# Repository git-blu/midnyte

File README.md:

# Midnyte LED tablet

Midnyte is an AVR-based resistive touchscreen tablet that uses a 16x24 RGB LED display.
74HC595 shift registers and TLC5940 16-channel PWM LED drivers drive the display and a Semtech SX8652 drives the 4-wire resistive touch panel for user input.
The device can switch between wall power and an internal Li-Ion battery pack.

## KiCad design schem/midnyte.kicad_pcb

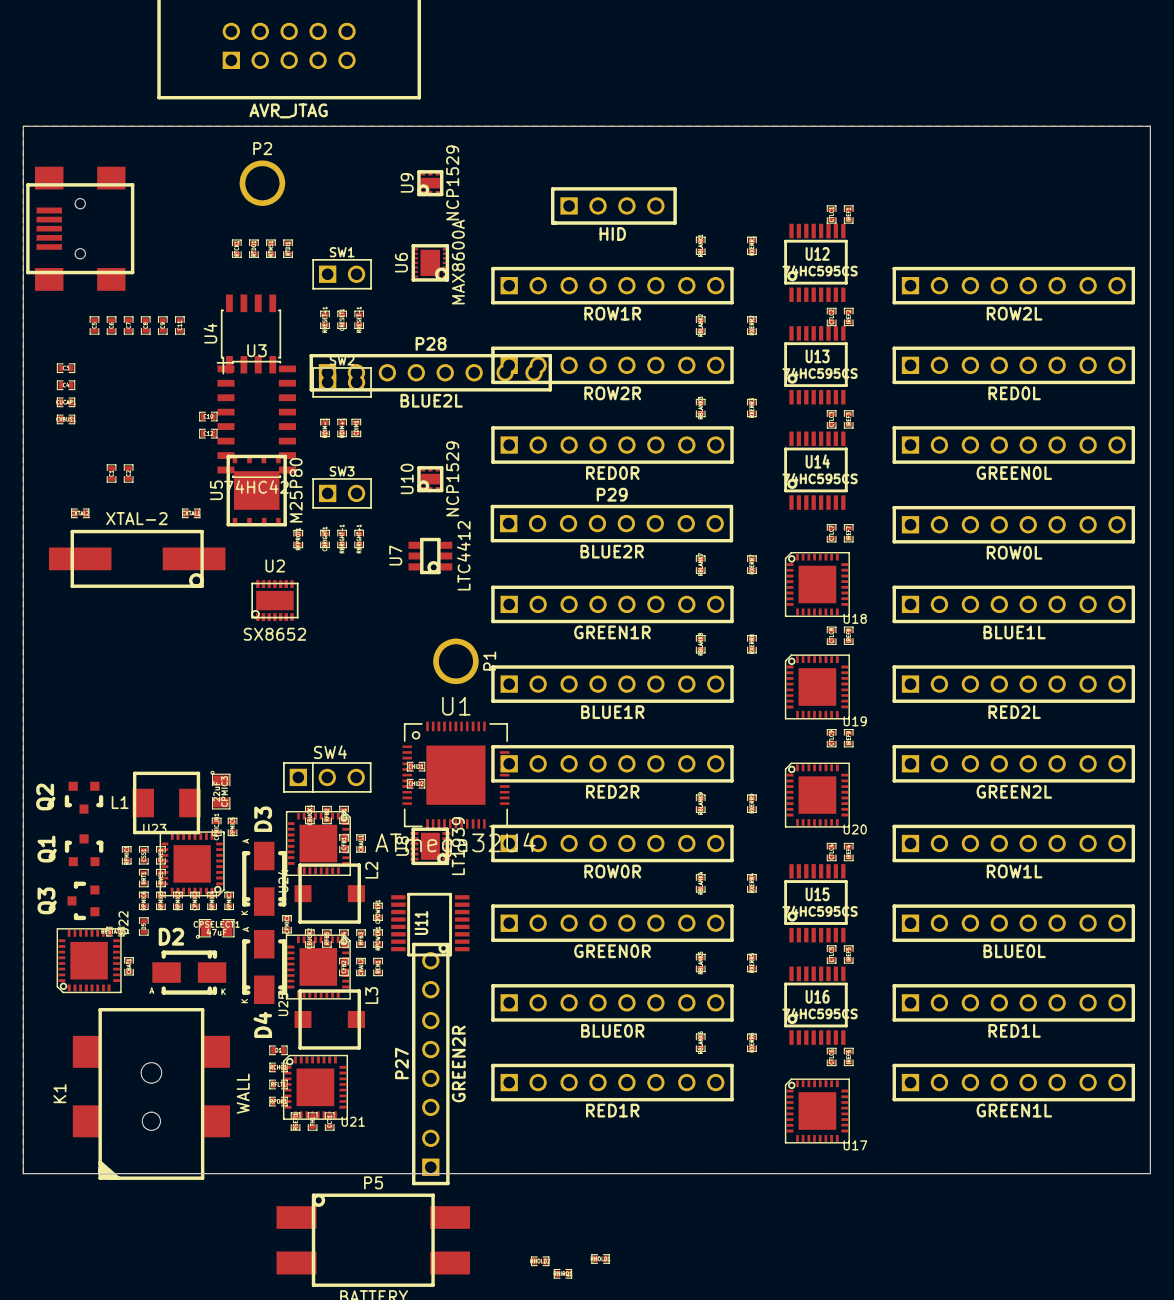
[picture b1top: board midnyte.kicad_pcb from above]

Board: 4 copper layers, 99.0 x 92.0 mm, 181 parts (0 on the bottom side), 302 nets, no tracks yet.

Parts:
C1, C2, C3, C4, C5, C6, C7, C8, C9, C10, C11, C12: 0.1uF; SMD-0402
CBAT1: 2.2uF; SMD-0402
CBRIGHT1: 0.1uF; SMD-0402
CBUCK1, CBUCK2: 4.7uF; SMD-0402
CCT1: 680nF; SMD-0402
CDIM1: 0.1uF; SMD-0402
CFB1, CFB2: 18pF; SMD-0402
CHID1: 1uF; SMD-0402
CHID2: 0.1uF; SMD-0402
CON1: USB-MINI-B; 10033526-N3212LF
CPMIC1: 0.47uF; SMD-0402
CPMIC2: 1uF; SMD-0402
CPMIC3: 22uF; SMD-0805
CPMIC_IN1: 2.2uF; SMD-0402
CPOWER1: 0.1uF; SMD-0402
CPSELECT1: 47uF; SMD-0805
CRAIL1, CRAIL2: 10uF; SMD-0402
CRESET1: 0.1uF; SMD-0402
CSS1: 0.47uF; SMD-0402
CTLC1, CTLC2, CTLC3, CTLC4, CTLC5, CTLC6, CTLC7, CTLC8, CTLC9: 0.1uF; SMD-0402
CUCAP1: 1uF; SMD-0402
CVBUS1: 0.1uF; SMD-0402
CVC1: 220pF; SMD-0402
CXTAL1, CXTAL2: 18pF; SMD-0402
D1, D5: DIODE; SMD-0402
D2, D3, D4: SCHOTTKY; Diode-SMA_Standard
IREF1, IREF2, IREF3, IREF4, IREF5, IREF6, IREF7, IREF8, IREF9: 7.68k; SMD-0402
K1: WALL; PJ-002AH-SMT
L1: 4.7uH; ASPI-0530LR-4R7M-T2
L2, L3: 2.2uH; LTF5022T-2R2N3R2-LC
P1, P2: HOLE-M3
P3: HID; pin_array_4x1
P4: AVR_JTAG; 302-S101
P5: BATTERY; 1954097-1
P6: ROW0L; pin_array_8x1
P7: ROW0R; pin_array_8x1
P8: ROW1L; pin_array_8x1
P9: ROW1R; pin_array_8x1
P10: ROW2L; pin_array_8x1
P11: ROW2R; pin_array_8x1
P12: RED0L; pin_array_8x1
P13: RED0R; pin_array_8x1
P14: GREEN0L; pin_array_8x1
P15: GREEN0R; pin_array_8x1
P16: BLUE0L; pin_array_8x1
P17: BLUE0R; pin_array_8x1
P18: RED1L; pin_array_8x1
P19: RED1R; pin_array_8x1
P20: GREEN1L; pin_array_8x1
P21: GREEN1R; pin_array_8x1
P22: BLUE1L; pin_array_8x1
P23: BLUE1R; pin_array_8x1
P24: RED2L; pin_array_8x1
P25: RED2R; pin_array_8x1
P26: GREEN2L; pin_array_8x1
P27: GREEN2R; pin_array_8x1
P28: BLUE2L; pin_array_8x1
P29: BLUE2R; pin_array_8x1
Q1, Q2: FQP27P06; SOT23_Transistor_RevB_14Mar2014
Q3: N-CHANNEL_FET; SOT23_Transistor_RevB_14Mar2014
RBLANK1, RBLANK2, RBLANK3, RBLANK4, RBLANK5, RBLANK6, RBLANK7, RBLANK8, RBLANK9: 10k; SMD-0402
RBRIGHT+1: 10k; SMD-0402
RBRIGHT-1: 100; SMD-0402
RCHG1: 660; SMD-0402
RDIM+1: 10k; SMD-0402
RDIM-1: 100; SMD-0402
REN1: 10k; SMD-0402
RFB1: 2.7M; SMD-0402
RFB2, RFB5: 597k; SMD-0402
RFB3: 4.32M; SMD-0402
RFB4: 80k; SMD-0402
RFLT1: 100k; SMD-0402
RFPROT1: 10k; SMD-0402
RHOLD1, RHOLD2: 10k; SMD-0402
RNIRQ1: 10k; SMD-0402
RPMIC1: 10k; SMD-0402
RPMIC2, RPMIC5: 42.2k; SMD-0402
RPMIC3, RPMIC6, RPMIC7: 8.06k; SMD-0402
RPMIC4: 100k; SMD-0402
RPOK1: 10k; SMD-0402
RPOWER1: 10k; SMD-0402
RPSTATUS1: 10k; SMD-0402
RRESET+1: 10k; SMD-0402
RRESET-1: 100; SMD-0402
RRT1: 40.2k; SMD-0402
RSETI1: 2k; SMD-0402
RTCK1: 100k; SMD-0402
RTDI1: 100k; SMD-0402
RTDO1: 100k; SMD-0402
RTMS1: 100k; SMD-0402
RVC1: 49.9k; SMD-0402
RXERR1, RXERR2, RXERR3, RXERR4, RXERR5, RXERR6, RXERR7, RXERR8, RXERR9: 10k; SMD-0402
SW1: RESET; pin_array_1x02
SW2: -BRIGHTNESS; pin_array_1x02
SW3: +BRIGHTNESS; pin_array_1x02
SW4: POWER; pin_array_1x03
TH1: 10k@25C; SMD-0402
U1: ATmega32U4; QFN-44-1EP
U2: SX8652
U3: 74HC42; SOIC-16_3.9x9.9mm_Pitch1.27mm
U4: 23LC1024; SOIC-8_3.9x4.9mm_Pitch1.27mm
U5: M25P80; VDFN-8
U6: MAX8600A; TDFN14
U7: LTC4412; TSOT-23
U8: LT1939; DFN12
U9, U10: NCP1529; UDFN6
U11, U12, U13, U14, U15, U16: 74HC595CS; TSSOP-16
U17, U18, U19, U20, U21, U22, U23, U24, U25: TLC5940; QFN-32-1EP
X1: XTAL-2; CSM-7X

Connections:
+3.3V: C1.1, C2.1, C3.1, C4.1, C5.1, C6.1, C7.1, C8.1, C9.1, C10.1, C11.1, C12.1, CFB1.1, CHID1.1, CHID2.1, CRAIL1.1, CTLC1.1, CTLC2.1, CTLC3.1, CTLC4.1, CTLC5.1, CTLC6.1, CTLC7.1, CTLC8.1, CTLC9.1, D1.1, L2.2, P4.4, RBLANK1.1, RBLANK2.1, RBLANK3.1, RBLANK4.1, RBLANK5.1, RBLANK6.1, RBLANK7.1, RBLANK8.1, RBLANK9.1, RBRIGHT+1.1, RDIM+1.1, RFB1.1, RFLT1.1, RFPROT1.1, RHOLD1.1, RHOLD2.1, RNIRQ1.1, RPMIC1.1, RPOK1.1, RPSTATUS1.1, RRESET+1.1, RTCK1.1, RTDI1.1, RTDO1.1, RTMS1.1, RXERR1.1, RXERR2.1, RXERR3.1, RXERR4.1, RXERR5.1, RXERR6.1, RXERR7.1, RXERR8.1, RXERR9.1, U1.2, U1.14, U1.24, U1.34, U1.42, U1.44, U2.2, U3.16, U4.8, U5.8, U11.16, U12.16, U13.16, U14.16, U15.16, U16.16, U17.27, U18.27, U19.27, U20.27, U21.27, U22.27, U23.27, U24.27, U25.27
+5V: CFB2.1, CRAIL2.1, L3.2, RFB3.1, U6.9, U6.12, U6.13
/+BRIGHTNESS: CBRIGHT1.1, RBRIGHT+1.2, RBRIGHT-1.1, U1.28
/-BRIGHTNESS: CDIM1.1, RDIM+1.2, RDIM-1.1, U1.29
/D+: CON1.3, U1.4
/D-: CON1.2, U1.3
/F_PROT: RFPROT1.2, U5.3
/MEM_CS0: U1.8, U3.15
/MEM_CS1: U1.40, U3.14
/MISO: U1.11, U2.10, U4.2, U5.2
/MOSI: U1.10, U2.9, U4.5, U5.5
/Midnyte Display/BLANK: RBLANK1.2, RBLANK2.2, RBLANK3.2, RBLANK4.2, RBLANK5.2, RBLANK6.2, RBLANK7.2, RBLANK8.2, RBLANK9.2, U1.18, U11.10, U12.10, U13.10, U14.10, U15.10, U16.10, U17.31, U18.31, U19.31, U20.31, U21.31, U22.31, U23.31, U24.31, U25.31
/Midnyte Display/COL0: U1.22, U17.2
/Midnyte Display/COL1: U1.26, U20.2
/Midnyte Display/COL2: U1.27, U23.2
/Midnyte Display/COLCLK: U1.32, U17.1, U18.1, U19.1, U20.1, U21.1, U22.1, U23.1, U24.1, U25.1
/Midnyte Display/DCPROG: U1.19, U17.25, U18.25, U19.25, U20.25, U21.25, U22.25, U23.25, U24.25, U25.25
/Midnyte Display/FRAMECLK: U1.31, U11.12, U12.12, U13.12, U14.12, U15.12, U16.12, U17.32, U18.32, U19.32, U20.32, U21.32, U22.32, U23.32, U24.32, U25.32
/Midnyte Display/GSCLK: U1.33, U17.24, U18.24, U19.24, U20.24, U21.24, U22.24, U23.24, U24.24, U25.24
/Midnyte Display/Midnyte LED Row 0/BLUE0L: P16.1, U19.4
/Midnyte Display/Midnyte LED Row 0/BLUE0R: P17.1, U19.14
/Midnyte Display/Midnyte LED Row 0/BLUE1L: P16.2, U19.5
/Midnyte Display/Midnyte LED Row 0/BLUE1R: P17.2, U19.15
/Midnyte Display/Midnyte LED Row 0/BLUE2L: P16.3, U19.6
/Midnyte Display/Midnyte LED Row 0/BLUE2R: P17.3, U19.16
/Midnyte Display/Midnyte LED Row 0/BLUE3L: P16.4, U19.7
/Midnyte Display/Midnyte LED Row 0/BLUE3R: P17.4, U19.17
/Midnyte Display/Midnyte LED Row 0/BLUE4L: P16.5, U19.8
/Midnyte Display/Midnyte LED Row 0/BLUE4R: P17.5, U19.18
/Midnyte Display/Midnyte LED Row 0/BLUE5L: P16.6, U19.9
/Midnyte Display/Midnyte LED Row 0/BLUE5R: P17.6, U19.19
/Midnyte Display/Midnyte LED Row 0/BLUE6L: P16.7, U19.10
/Midnyte Display/Midnyte LED Row 0/BLUE6R: P17.7, U19.20
/Midnyte Display/Midnyte LED Row 0/BLUE7L: P16.8, U19.11
/Midnyte Display/Midnyte LED Row 0/BLUE7R: P17.8, U19.21
/Midnyte Display/Midnyte LED Row 0/GREEN0L: P14.1, U18.4
/Midnyte Display/Midnyte LED Row 0/GREEN0R: P15.1, U18.14
/Midnyte Display/Midnyte LED Row 0/GREEN1L: P14.2, U18.5
/Midnyte Display/Midnyte LED Row 0/GREEN1R: P15.2, U18.15
/Midnyte Display/Midnyte LED Row 0/GREEN2L: P14.3, U18.6
/Midnyte Display/Midnyte LED Row 0/GREEN2R: P15.3, U18.16
/Midnyte Display/Midnyte LED Row 0/GREEN3L: P14.4, U18.7
/Midnyte Display/Midnyte LED Row 0/GREEN3R: P15.4, U18.17
/Midnyte Display/Midnyte LED Row 0/GREEN4L: P14.5, U18.8
/Midnyte Display/Midnyte LED Row 0/GREEN4R: P15.5, U18.18
/Midnyte Display/Midnyte LED Row 0/GREEN5L: P14.6, U18.9
/Midnyte Display/Midnyte LED Row 0/GREEN5R: P15.6, U18.19
/Midnyte Display/Midnyte LED Row 0/GREEN6L: P14.7, U18.10
/Midnyte Display/Midnyte LED Row 0/GREEN6R: P15.7, U18.20
/Midnyte Display/Midnyte LED Row 0/GREEN7L: P14.8, U18.11
/Midnyte Display/Midnyte LED Row 0/GREEN7R: P15.8, U18.21
/Midnyte Display/Midnyte LED Row 0/IREF0: IREF1.1, U17.26
/Midnyte Display/Midnyte LED Row 0/IREF1: IREF2.1, U18.26
/Midnyte Display/Midnyte LED Row 0/IREF2: IREF3.1, U19.26
/Midnyte Display/Midnyte LED Row 0/RED0L: P12.1, U17.4
/Midnyte Display/Midnyte LED Row 0/RED0R: P13.1, U17.14
/Midnyte Display/Midnyte LED Row 0/RED1L: P12.2, U17.5
/Midnyte Display/Midnyte LED Row 0/RED1R: P13.2, U17.15
/Midnyte Display/Midnyte LED Row 0/RED2L: P12.3, U17.6
/Midnyte Display/Midnyte LED Row 0/RED2R: P13.3, U17.16
/Midnyte Display/Midnyte LED Row 0/RED3L: P12.4, U17.7
/Midnyte Display/Midnyte LED Row 0/RED3R: P13.4, U17.17
/Midnyte Display/Midnyte LED Row 0/RED4L: P12.5, U17.8
/Midnyte Display/Midnyte LED Row 0/RED4R: P13.5, U17.18
/Midnyte Display/Midnyte LED Row 0/RED5L: P12.6, U17.9
/Midnyte Display/Midnyte LED Row 0/RED5R: P13.6, U17.19
/Midnyte Display/Midnyte LED Row 0/RED6L: P12.7, U17.10
/Midnyte Display/Midnyte LED Row 0/RED6R: P13.7, U17.20
/Midnyte Display/Midnyte LED Row 0/RED7L: P12.8, U17.11
/Midnyte Display/Midnyte LED Row 0/RED7R: P13.8, U17.21
/Midnyte Display/Midnyte LED Row 0/SER1: U18.23, U19.2
/Midnyte Display/Midnyte LED Row 1/BLUE0L: P22.1, U22.4
/Midnyte Display/Midnyte LED Row 1/BLUE0R: P23.1, U22.14
/Midnyte Display/Midnyte LED Row 1/BLUE1L: P22.2, U22.5
/Midnyte Display/Midnyte LED Row 1/BLUE1R: P23.2, U22.15
/Midnyte Display/Midnyte LED Row 1/BLUE2L: P22.3, U22.6
/Midnyte Display/Midnyte LED Row 1/BLUE2R: P23.3, U22.16
/Midnyte Display/Midnyte LED Row 1/BLUE3L: P22.4, U22.7
/Midnyte Display/Midnyte LED Row 1/BLUE3R: P23.4, U22.17
/Midnyte Display/Midnyte LED Row 1/BLUE4L: P22.5, U22.8
/Midnyte Display/Midnyte LED Row 1/BLUE4R: P23.5, U22.18
/Midnyte Display/Midnyte LED Row 1/BLUE5L: P22.6, U22.9
/Midnyte Display/Midnyte LED Row 1/BLUE5R: P23.6, U22.19
/Midnyte Display/Midnyte LED Row 1/BLUE6L: P22.7, U22.10
/Midnyte Display/Midnyte LED Row 1/BLUE6R: P23.7, U22.20
/Midnyte Display/Midnyte LED Row 1/BLUE7L: P22.8, U22.11
/Midnyte Display/Midnyte LED Row 1/BLUE7R: P23.8, U22.21
/Midnyte Display/Midnyte LED Row 1/GREEN0L: P20.1, U21.4
/Midnyte Display/Midnyte LED Row 1/GREEN0R: P21.1, U21.14
/Midnyte Display/Midnyte LED Row 1/GREEN1L: P20.2, U21.5
/Midnyte Display/Midnyte LED Row 1/GREEN1R: P21.2, U21.15
/Midnyte Display/Midnyte LED Row 1/GREEN2L: P20.3, U21.6
/Midnyte Display/Midnyte LED Row 1/GREEN2R: P21.3, U21.16
/Midnyte Display/Midnyte LED Row 1/GREEN3L: P20.4, U21.7
/Midnyte Display/Midnyte LED Row 1/GREEN3R: P21.4, U21.17
/Midnyte Display/Midnyte LED Row 1/GREEN4L: P20.5, U21.8
/Midnyte Display/Midnyte LED Row 1/GREEN4R: P21.5, U21.18
/Midnyte Display/Midnyte LED Row 1/GREEN5L: P20.6, U21.9
/Midnyte Display/Midnyte LED Row 1/GREEN5R: P21.6, U21.19
/Midnyte Display/Midnyte LED Row 1/GREEN6L: P20.7, U21.10
/Midnyte Display/Midnyte LED Row 1/GREEN6R: P21.7, U21.20
/Midnyte Display/Midnyte LED Row 1/GREEN7L: P20.8, U21.11
/Midnyte Display/Midnyte LED Row 1/GREEN7R: P21.8, U21.21
/Midnyte Display/Midnyte LED Row 1/IREF0: IREF4.1, U20.26
/Midnyte Display/Midnyte LED Row 1/IREF1: IREF5.1, U21.26
/Midnyte Display/Midnyte LED Row 1/IREF2: IREF6.1, U22.26
/Midnyte Display/Midnyte LED Row 1/RED0L: P18.1, U20.4
/Midnyte Display/Midnyte LED Row 1/RED0R: P19.1, U20.14
/Midnyte Display/Midnyte LED Row 1/RED1L: P18.2, U20.5
/Midnyte Display/Midnyte LED Row 1/RED1R: P19.2, U20.15
/Midnyte Display/Midnyte LED Row 1/RED2L: P18.3, U20.6
/Midnyte Display/Midnyte LED Row 1/RED2R: P19.3, U20.16
/Midnyte Display/Midnyte LED Row 1/RED3L: P18.4, U20.7
/Midnyte Display/Midnyte LED Row 1/RED3R: P19.4, U20.17
/Midnyte Display/Midnyte LED Row 1/RED4L: P18.5, U20.8
/Midnyte Display/Midnyte LED Row 1/RED4R: P19.5, U20.18
/Midnyte Display/Midnyte LED Row 1/RED5L: P18.6, U20.9
/Midnyte Display/Midnyte LED Row 1/RED5R: P19.6, U20.19
/Midnyte Display/Midnyte LED Row 1/RED6L: P18.7, U20.10
/Midnyte Display/Midnyte LED Row 1/RED6R: P19.7, U20.20
/Midnyte Display/Midnyte LED Row 1/RED7L: P18.8, U20.11
/Midnyte Display/Midnyte LED Row 1/RED7R: P19.8, U20.21
/Midnyte Display/Midnyte LED Row 1/SER1: U21.23, U22.2
/Midnyte Display/Midnyte LED Row 2/BLUE0L: P28.1, U25.4
/Midnyte Display/Midnyte LED Row 2/BLUE0R: P29.1, U25.14
/Midnyte Display/Midnyte LED Row 2/BLUE1L: P28.2, U25.5
/Midnyte Display/Midnyte LED Row 2/BLUE1R: P29.2, U25.15
/Midnyte Display/Midnyte LED Row 2/BLUE2L: P28.3, U25.6
/Midnyte Display/Midnyte LED Row 2/BLUE2R: P29.3, U25.16
/Midnyte Display/Midnyte LED Row 2/BLUE3L: P28.4, U25.7
/Midnyte Display/Midnyte LED Row 2/BLUE3R: P29.4, U25.17
/Midnyte Display/Midnyte LED Row 2/BLUE4L: P28.5, U25.8
/Midnyte Display/Midnyte LED Row 2/BLUE4R: P29.5, U25.18
/Midnyte Display/Midnyte LED Row 2/BLUE5L: P28.6, U25.9
/Midnyte Display/Midnyte LED Row 2/BLUE5R: P29.6, U25.19
/Midnyte Display/Midnyte LED Row 2/BLUE6L: P28.7, U25.10
/Midnyte Display/Midnyte LED Row 2/BLUE6R: P29.7, U25.20
/Midnyte Display/Midnyte LED Row 2/BLUE7L: P28.8, U25.11
/Midnyte Display/Midnyte LED Row 2/BLUE7R: P29.8, U25.21
/Midnyte Display/Midnyte LED Row 2/GREEN0L: P26.1, U24.4
/Midnyte Display/Midnyte LED Row 2/GREEN0R: P27.1, U24.14
/Midnyte Display/Midnyte LED Row 2/GREEN1L: P26.2, U24.5
/Midnyte Display/Midnyte LED Row 2/GREEN1R: P27.2, U24.15
/Midnyte Display/Midnyte LED Row 2/GREEN2L: P26.3, U24.6
/Midnyte Display/Midnyte LED Row 2/GREEN2R: P27.3, U24.16
/Midnyte Display/Midnyte LED Row 2/GREEN3L: P26.4, U24.7
/Midnyte Display/Midnyte LED Row 2/GREEN3R: P27.4, U24.17
/Midnyte Display/Midnyte LED Row 2/GREEN4L: P26.5, U24.8
/Midnyte Display/Midnyte LED Row 2/GREEN4R: P27.5, U24.18
/Midnyte Display/Midnyte LED Row 2/GREEN5L: P26.6, U24.9
/Midnyte Display/Midnyte LED Row 2/GREEN5R: P27.6, U24.19
/Midnyte Display/Midnyte LED Row 2/GREEN6L: P26.7, U24.10
/Midnyte Display/Midnyte LED Row 2/GREEN6R: P27.7, U24.20
/Midnyte Display/Midnyte LED Row 2/GREEN7L: P26.8, U24.11
/Midnyte Display/Midnyte LED Row 2/GREEN7R: P27.8, U24.21
/Midnyte Display/Midnyte LED Row 2/IREF0: IREF7.1, U23.26
/Midnyte Display/Midnyte LED Row 2/IREF1: IREF8.1, U24.26
/Midnyte Display/Midnyte LED Row 2/IREF2: IREF9.1, U25.26
/Midnyte Display/Midnyte LED Row 2/RED0L: P24.1, U23.4
/Midnyte Display/Midnyte LED Row 2/RED0R: P25.1, U23.14
/Midnyte Display/Midnyte LED Row 2/RED1L: P24.2, U23.5
/Midnyte Display/Midnyte LED Row 2/RED1R: P25.2, U23.15
/Midnyte Display/Midnyte LED Row 2/RED2L: P24.3, U23.6
/Midnyte Display/Midnyte LED Row 2/RED2R: P25.3, U23.16
/Midnyte Display/Midnyte LED Row 2/RED3L: P24.4, U23.7
/Midnyte Display/Midnyte LED Row 2/RED3R: P25.4, U23.17
/Midnyte Display/Midnyte LED Row 2/RED4L: P24.5, U23.8
/Midnyte Display/Midnyte LED Row 2/RED4R: P25.5, U23.18
/Midnyte Display/Midnyte LED Row 2/RED5L: P24.6, U23.9
/Midnyte Display/Midnyte LED Row 2/RED5R: P25.6, U23.19
/Midnyte Display/Midnyte LED Row 2/RED6L: P24.7, U23.10
/Midnyte Display/Midnyte LED Row 2/RED6R: P25.7, U23.20
/Midnyte Display/Midnyte LED Row 2/RED7L: P24.8, U23.11
/Midnyte Display/Midnyte LED Row 2/RED7R: P25.8, U23.21
/Midnyte Display/Midnyte LED Row 2/SER1: U24.23, U25.2
/Midnyte Display/ROW0: U1.20, U11.14
/Midnyte Display/ROW0L: P6.1, U11.15
/Midnyte Display/ROW0R: P7.1, U14.15
/Midnyte Display/ROW1: U1.21, U12.14
/Midnyte Display/ROW1L: P6.2, U11.1
/Midnyte Display/ROW1R: P7.2, U14.1
/Midnyte Display/ROW2: U1.25, U13.14
/Midnyte Display/ROW2L: P6.3, U11.2
/Midnyte Display/ROW2R: P7.3, U14.2
/Midnyte Display/ROW3L: P6.4, U11.3
/Midnyte Display/ROW3R: P7.4, U14.3
/Midnyte Display/ROW4L: P6.5, U11.4
/Midnyte Display/ROW4R: P7.5, U14.4
/Midnyte Display/ROW5L: P6.6, U11.5
/Midnyte Display/ROW5R: P7.6, U14.5
/Midnyte Display/ROW6L: P6.7, U11.6
/Midnyte Display/ROW6R: P7.7, U14.6
/Midnyte Display/ROW7L: P6.8, U11.7
/Midnyte Display/ROW7R: P7.8, U14.7
/Midnyte Display/ROW8L: P8.1, U12.15
/Midnyte Display/ROW8R: P9.1, U15.15
/Midnyte Display/ROW9L: P8.2, U12.1
/Midnyte Display/ROW9R: P9.2, U15.1
/Midnyte Display/ROW10L: P8.3, U12.2
/Midnyte Display/ROW10R: P9.3, U15.2
/Midnyte Display/ROW11L: P8.4, U12.3
/Midnyte Display/ROW11R: P9.4, U15.3
/Midnyte Display/ROW12L: P8.5, U12.4
/Midnyte Display/ROW12R: P9.5, U15.4
/Midnyte Display/ROW13L: P8.6, U12.5
/Midnyte Display/ROW13R: P9.6, U15.5
/Midnyte Display/ROW14L: P8.7, U12.6
/Midnyte Display/ROW14R: P9.7, U15.6
/Midnyte Display/ROW15L: P8.8, U12.7
/Midnyte Display/ROW15R: P9.8, U15.7
/Midnyte Display/ROW16L: P10.1, U13.15
/Midnyte Display/ROW16R: P11.1, U16.15
/Midnyte Display/ROW17L: P10.2, U13.1
/Midnyte Display/ROW17R: P11.2, U16.1
/Midnyte Display/ROW18L: P10.3, U13.2
/Midnyte Display/ROW18R: P11.3, U16.2
/Midnyte Display/ROW19L: P10.4, U13.3
/Midnyte Display/ROW19R: P11.4, U16.3
/Midnyte Display/ROW20L: P10.5, U13.4
/Midnyte Display/ROW20R: P11.5, U16.4
/Midnyte Display/ROW21L: P10.6, U13.5
/Midnyte Display/ROW21R: P11.6, U16.5
/Midnyte Display/ROW22L: P10.7, U13.6
/Midnyte Display/ROW22R: P11.7, U16.6
/Midnyte Display/ROW23L: P10.8, U13.7
/Midnyte Display/ROW23R: P11.8, U16.7
/Midnyte Display/ROWCLK: U1.1, U11.11, U12.11, U13.11, U14.11, U15.11, U16.11
/Midnyte Display/SER2: U13.9, U16.14
/Midnyte Display/VPROG: U1.41, U17.3, U18.3, U19.3, U20.3, U21.3, U22.3, U23.3, U24.3, U25.3
/Midnyte Power/BAT+: CBAT1.1, P5.1, Q1.2, U6.1, U6.7, U7.1
/Midnyte Power/PMIC_IN: CPMIC_IN1.1, CPSELECT1.1, D2.2, Q1.3, U8.1
/Midnyte Power/PMIC_OUT: CBUCK1.1, CBUCK2.1, CPMIC3.1, D4.1, L1.2, REN1.1, RPMIC5.1, SW4.1, U9.3, U10.3
/Midnyte Power/POWER_STATUS: Q3.3, RPSTATUS1.2, U1.12
/Midnyte Power/WALL: D2.1, K1.1, U7.6
/NIRQ: RNIRQ1.2, U1.30, U2.11
/SCLK: U1.9, U2.8, U4.6, U5.6
/TCK: P4.1, RTCK1.2, U1.39
/TDI: P4.9, RTDI1.2, U1.36
/TDO: P4.3, RTDO1.2, U1.37
/TMS: P4.5, RTMS1.2, U1.38
/UCAP: CUCAP1.1, U1.6
/VBUS: CON1.1, CVBUS1.1, U1.7
/XTAL1: CXTAL1.1, U1.17, X1.1
/XTAL2: CXTAL2.1, U1.16, X1.2
/~MEM_CS0: U3.1, U4.1
/~MEM_CS1: U3.2, U5.1
/~MEM_CS2: U2.12, U3.3
GND: C1.2, C2.2, C3.2, C4.2, C5.2, C6.2, C7.2, C8.2, C9.2, C10.2, C11.2, C12.2, CBAT1.2, CBRIGHT1.2, CBUCK1.2, CBUCK2.2, CCT1.2, CDIM1.2, CHID1.2, CHID2.2, CON1.5, CON1.6, CON1.7, CON1.8, CON1.9, CPMIC2.2, CPMIC3.2, CPMIC_IN1.2, CPOWER1.2, CPSELECT1.2, CRAIL1.2, CRAIL2.2, CRESET1.2, CSS1.2, CTLC1.2, CTLC2.2, CTLC3.2, CTLC4.2, CTLC5.2, CTLC6.2, CTLC7.2, CTLC8.2, CTLC9.2, CUCAP1.2, CVBUS1.2, CXTAL1.2, CXTAL2.2, D3.1, IREF1.2, IREF2.2, IREF3.2, IREF4.2, IREF5.2, IREF6.2, IREF7.2, IREF8.2, IREF9.2, K1.2, K1.3, P1.1, P2.1, P4.2, P4.10, P5.2, Q2.3, Q3.2, RFB2.2, RFB5.2, RPMIC3.2, RPMIC7.2, RRT1.2, RSETI1.2, RVC1.2, SW1.1, SW2.2, SW3.2, SW4.3, TH1.2, U1.5, U1.15, U1.23, U1.35, U1.43, U1.45, U2.1, U2.7, U2.15, U3.8, U3.12, U3.13, U4.4, U5.4, U5.9, U6.4, U6.8, U6.15, U7.2, U7.3, U8.13, U9.2, U9.4, U9.7, U10.2, U10.4, U10.7, U11.8, U11.13, U12.8, U12.13, U13.8, U13.13, U14.8, U14.13, U15.8, U15.13, U16.8, U16.13, U17.30, U17.33, U18.30, U18.33, U19.30, U19.33, U20.30, U20.33, U21.30, U21.33, U22.30, U22.33, U23.30, U23.33, U24.30, U24.33, U25.30, U25.33
unnamed: CCT1.1, U6.5
unnamed: CFB1.2, RFB1.2, RFB2.1, U9.1
unnamed: CFB2.2, RFB4.2, RFB5.1, U10.1
unnamed: CPMIC1.1, D4.2, U8.11
unnamed: CPMIC1.2, D3.2, L1.1, U8.12
unnamed: CPMIC2.1, RPMIC2.1, RPMIC4.1, RPMIC6.1, U8.10
unnamed: CPOWER1.1, RPOWER1.2, SW4.2
unnamed: CRESET1.1, P4.6, RRESET+1.2, RRESET-1.2, U1.13, U2.13
unnamed: CSS1.1, U8.3
unnamed: CVC1.1, U8.5
unnamed: CVC1.2, RVC1.1
unnamed: D1.2, RCHG1.1
unnamed: D5.1, RPMIC6.2
unnamed: D5.2, Q2.2
unnamed: L2.1, U9.5
unnamed: L3.1, U10.5
unnamed: P3.1, U2.6
unnamed: P3.2, U2.5
unnamed: P3.3, U2.4
unnamed: P3.4, U2.3
unnamed: Q1.1, U7.5
unnamed: Q2.1, RPMIC4.2, U8.4
unnamed: Q3.1, U7.4
unnamed: RBRIGHT-1.2, SW3.1
unnamed: RCHG1.2, U6.11
unnamed: RDIM-1.2, SW2.1
unnamed: REN1.2, U10.6
unnamed: RFB3.2, RFB4.1
unnamed: RFLT1.2, U6.14
unnamed: RHOLD1.2, U4.7
unnamed: RHOLD2.2, U5.7
unnamed: RPMIC1.2, U8.7
unnamed: RPMIC2.2, RPMIC3.1, U8.9
unnamed: RPMIC5.2, RPMIC7.1, U8.8
unnamed: RPOK1.2, U6.10
unnamed: RPOWER1.1, U9.6
unnamed: RRESET-1.1, SW1.2
unnamed: RRT1.1, U8.6
unnamed: RSETI1.1, U6.2
unnamed: RXERR1.2, U17.22
unnamed: RXERR2.2, U18.22
unnamed: RXERR3.2, U19.22
unnamed: RXERR4.2, U20.22
unnamed: RXERR5.2, U21.22
unnamed: RXERR6.2, U22.22
unnamed: RXERR7.2, U23.22
unnamed: RXERR8.2, U24.22
unnamed: RXERR9.2, U25.22
unnamed: TH1.1, U6.3
unnamed: U11.9, U14.14
unnamed: U12.9, U15.14
unnamed: U17.23, U18.2
unnamed: U20.23, U21.2
unnamed: U23.23, U24.2

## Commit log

2016-11-06 Updated .gitignore with project specific file types
2016-11-06 Initial commit of firmware
2016-11-06 Initial commit for board design
2016-11-06 Updated the README with a little information about the device
2016-11-07 Fixed AVR MCU frequency
2016-11-07 Cleanup trailing whitespace
2016-11-07 Moved setup of display driver pins to DisplayDriver construction
2016-11-07 Small cleanup
2016-11-07 Added VIM swap files to ignore list
2016-12-26 Touch event will modify internal state, so removing const qualifer
2016-12-26 Added blank default destructor
2016-12-29 Move 'currentColor' ownership to Display + cleanup
